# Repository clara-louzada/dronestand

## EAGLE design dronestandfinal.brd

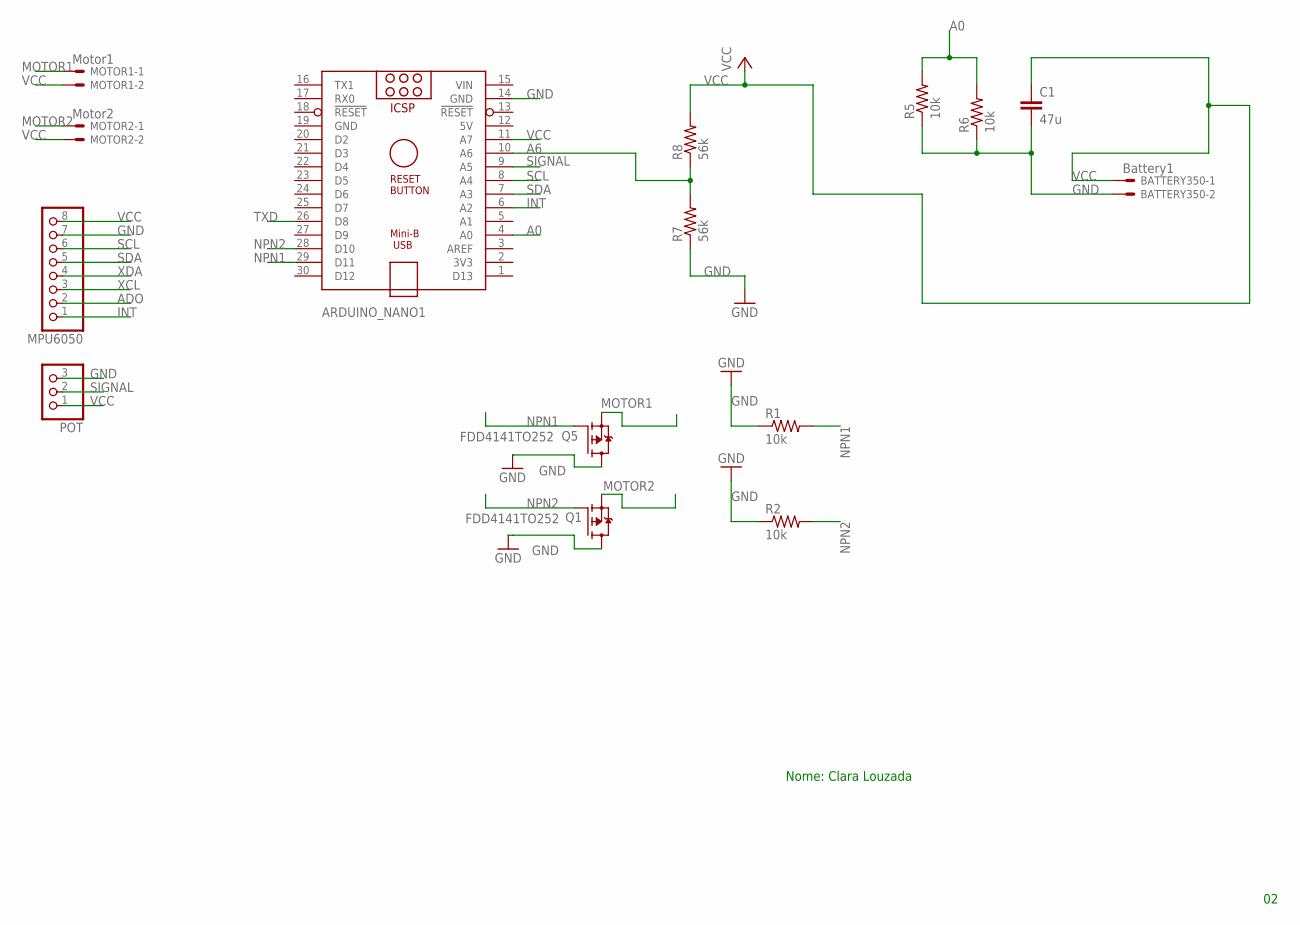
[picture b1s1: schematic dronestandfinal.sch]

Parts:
ARDUINO_NANO1: ARDUINO_NANO
BATTERY350: Battery1; JST-XH-02-PACKAGE-LONG-PAD
C1: 47u; C2.5-3
MOTOR1: Motor1; JST-XH-02-PACKAGE-LONG-PAD
MOTOR2: Motor2; JST-XH-02-PACKAGE-LONG-PAD
MPU6050: PINHD-1X8; 1X08
POT: PINHD-1X3; 1X03
Q1, Q5: FDD4141TO252; TO252
R1, R2, R5, R6: 10k; 0204/7
R7, R8: 56k; 0204/7

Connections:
5V: ARDUINO_NANO1.12 (5V)
A0: ARDUINO_NANO1.4 (A0), R5.2, R6.2
A6: ARDUINO_NANO1.10 (A6), R7.2, R8.1
ADO: MPU6050.2
GND: ARDUINO_NANO1.14 (GND), ARDUINO_NANO1.19 (GND), BATTERY350.2, C1.2, MPU6050.7, POT.3, Q1.3 (D), Q5.3 (D), R1.1, R2.1, R5.1, R6.1, R7.1
INT: ARDUINO_NANO1.6 (A2), MPU6050.1
MOTOR1: MOTOR1.1, Q5.2 (S)
MOTOR2: MOTOR2.1, Q1.2 (S)
NPN1: ARDUINO_NANO1.29 (D11), Q5.1 (G), R1.2
NPN2: ARDUINO_NANO1.28 (D10), Q1.1 (G), R2.2
SCL: ARDUINO_NANO1.8 (A4), MPU6050.6
SDA: ARDUINO_NANO1.7 (A3), MPU6050.5
SIGNAL: ARDUINO_NANO1.9 (A5), POT.2
TXD: ARDUINO_NANO1.26 (D8)
VCC: ARDUINO_NANO1.11 (A7), BATTERY350.1, C1.1, MOTOR1.2, MOTOR2.2, MPU6050.8, POT.1, R8.2
VIN: ARDUINO_NANO1.15 (VIN)
XCL: MPU6050.3
XDA: MPU6050.4

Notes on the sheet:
Nome: Clara Louzada

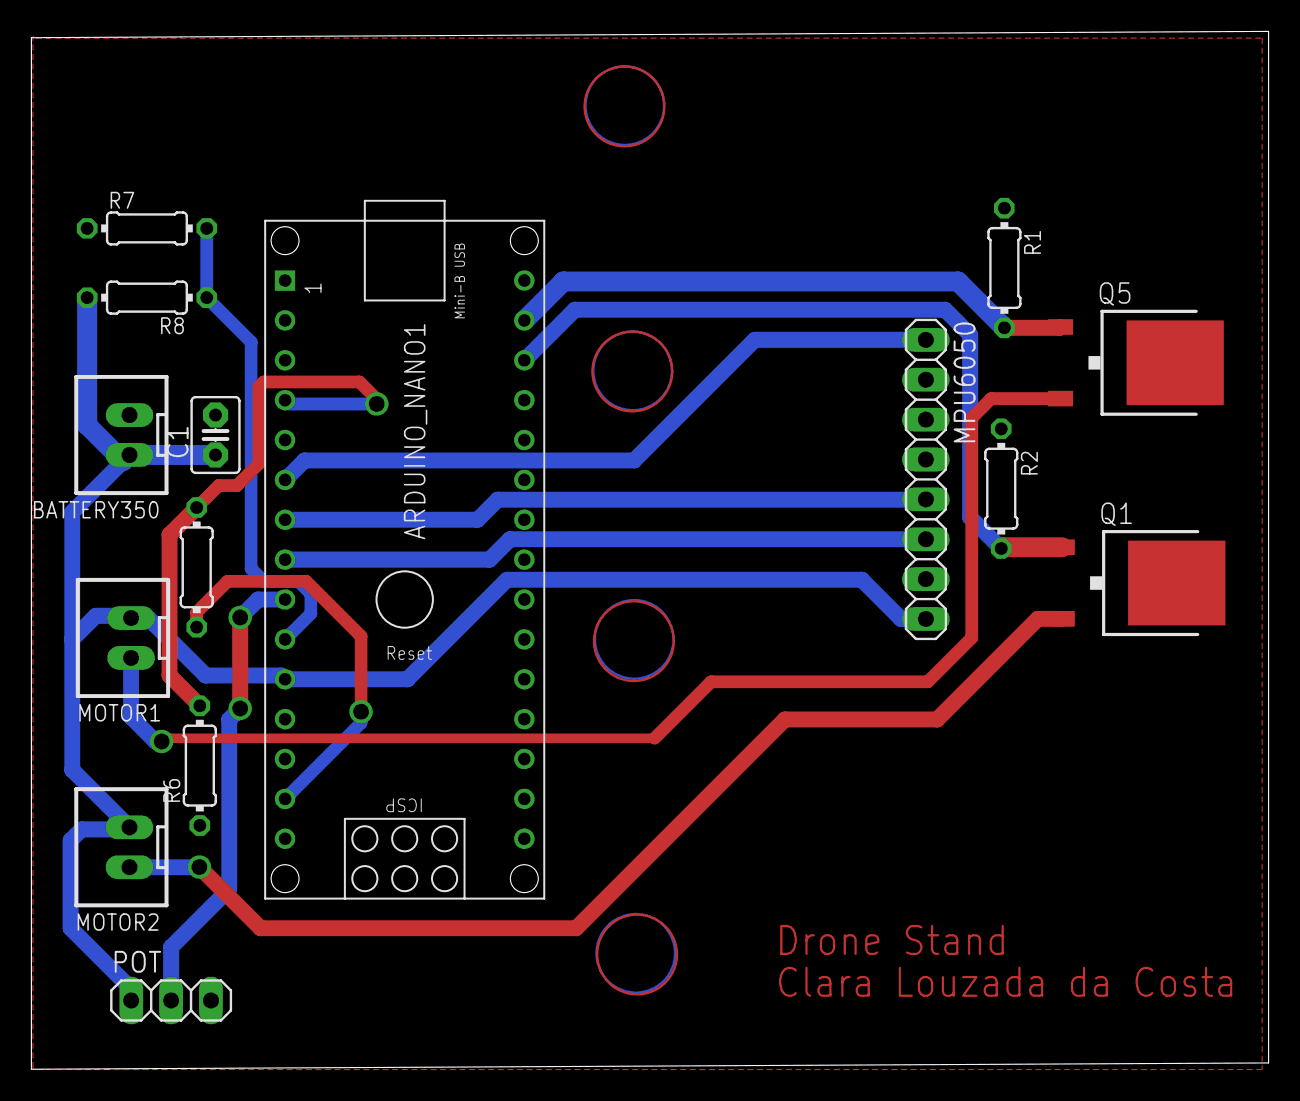
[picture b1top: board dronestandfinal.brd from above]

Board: 2 copper layers, 78.8 x 66.1 mm, 15 parts (0 on the bottom side), 12 nets.

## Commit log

2019-06-18 First commit of the control board
2019-06-19 Second commit of drone stand control board
2019-08-21 Drone stand final
